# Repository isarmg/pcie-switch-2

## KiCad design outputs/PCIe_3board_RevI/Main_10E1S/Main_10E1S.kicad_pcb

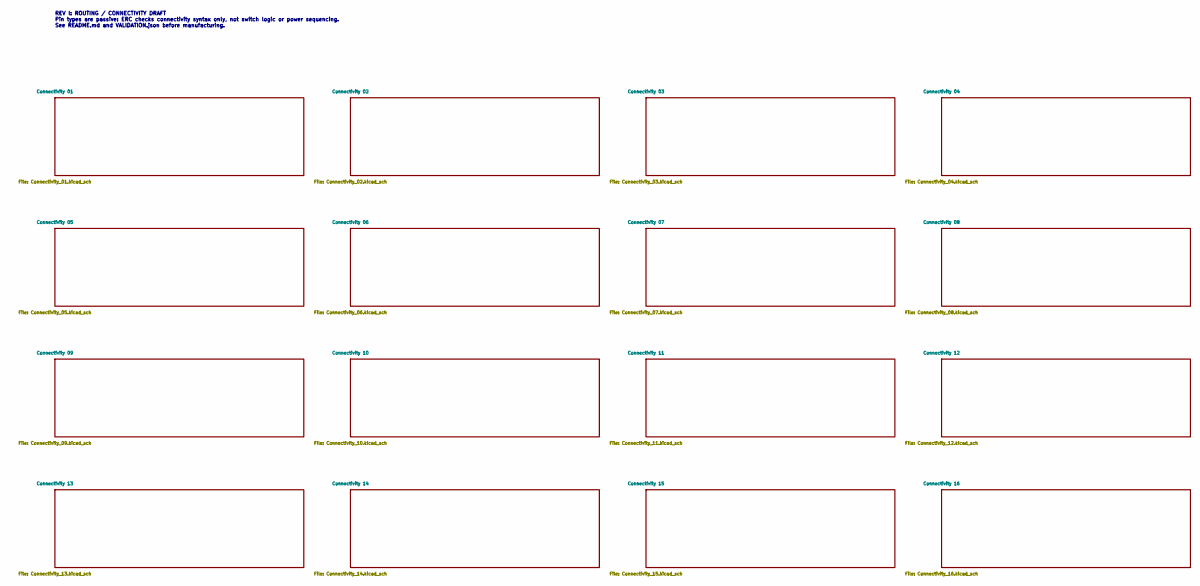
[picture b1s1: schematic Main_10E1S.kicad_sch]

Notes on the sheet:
REV I: ROUTING / CONNECTIVITY DRAFT Pin types are passive: ERC checks connectivity syntax only, not switch logic or power sequencing. See README.md and VALIDATION.json before manufacturing.

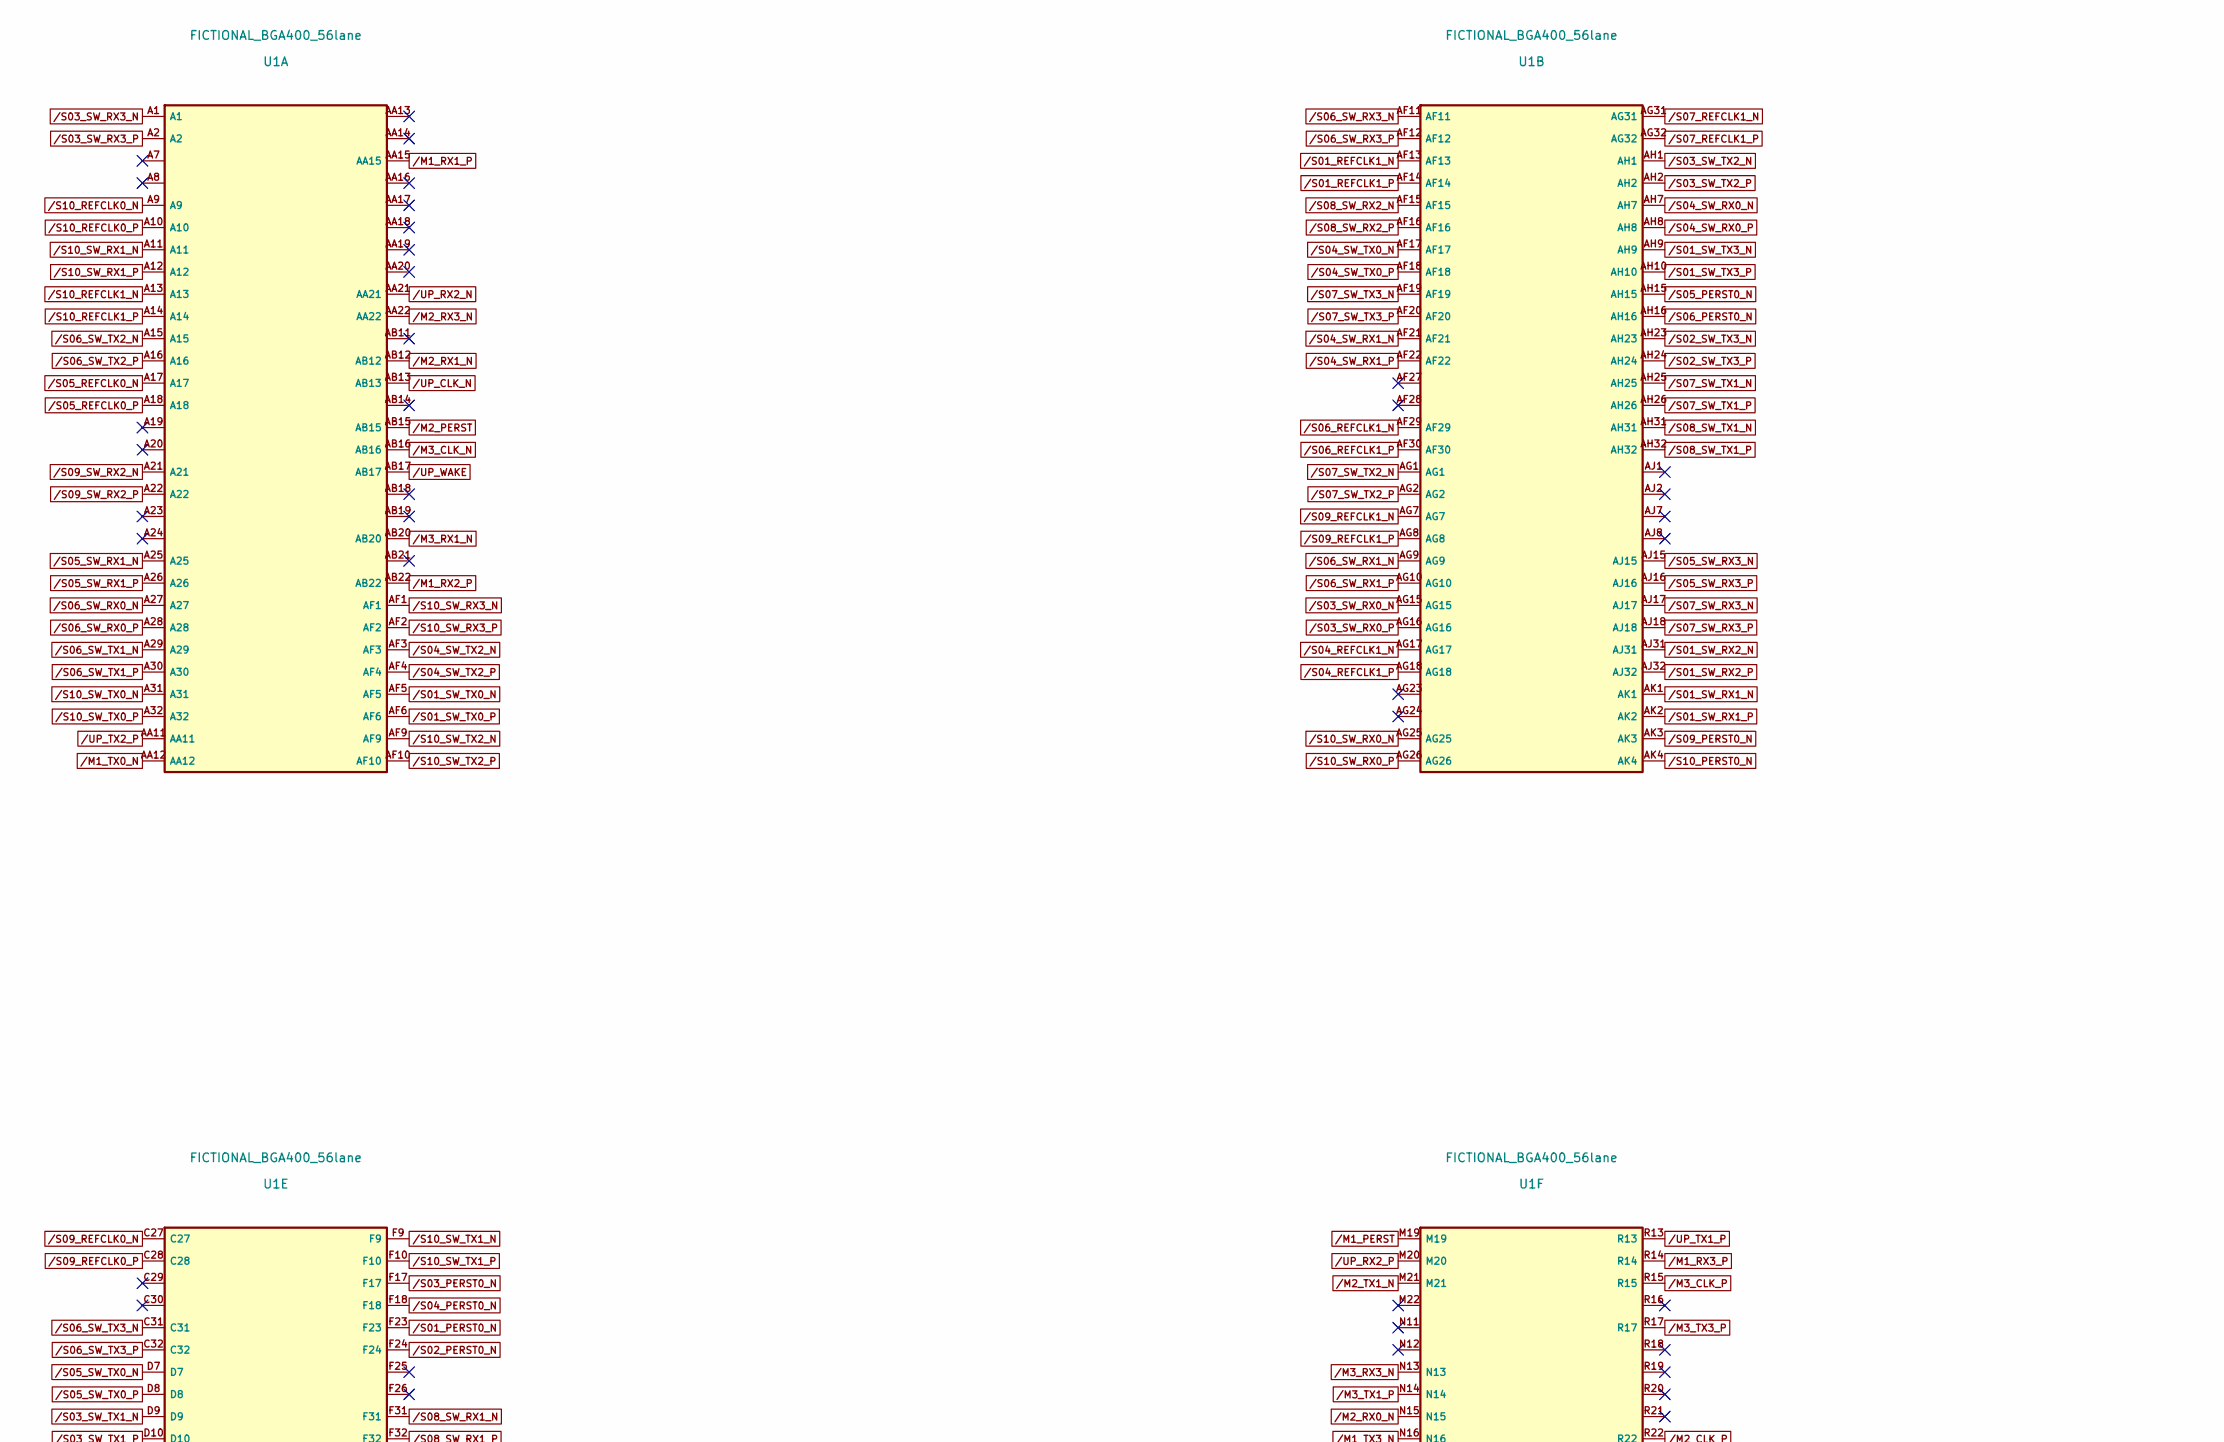
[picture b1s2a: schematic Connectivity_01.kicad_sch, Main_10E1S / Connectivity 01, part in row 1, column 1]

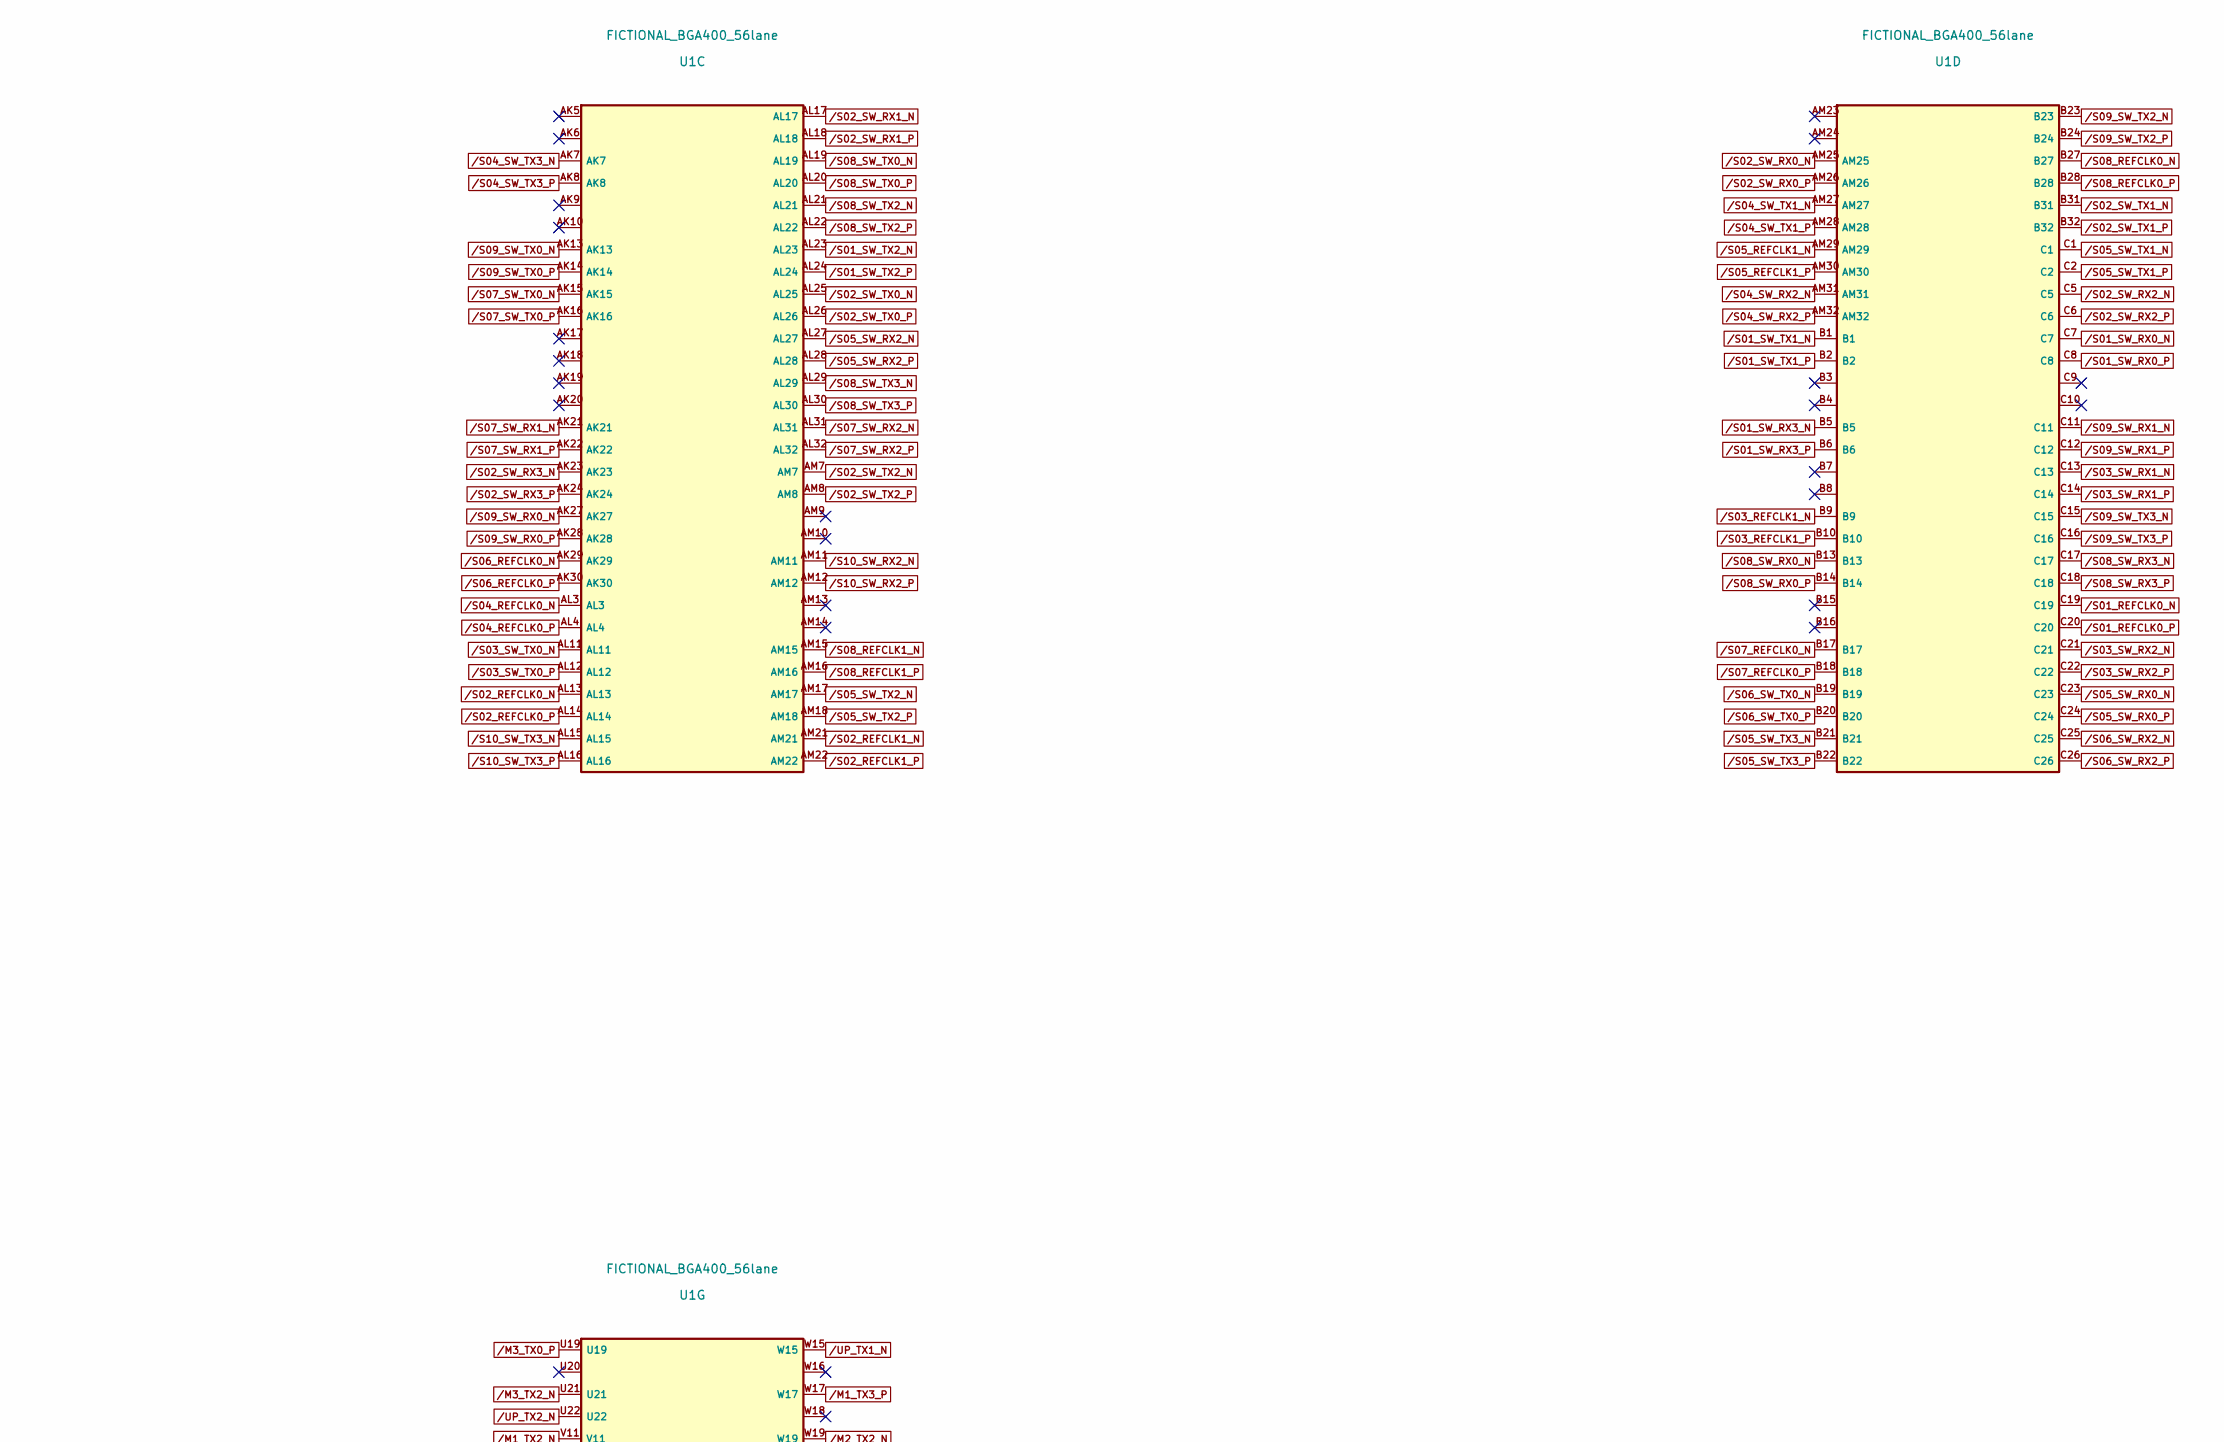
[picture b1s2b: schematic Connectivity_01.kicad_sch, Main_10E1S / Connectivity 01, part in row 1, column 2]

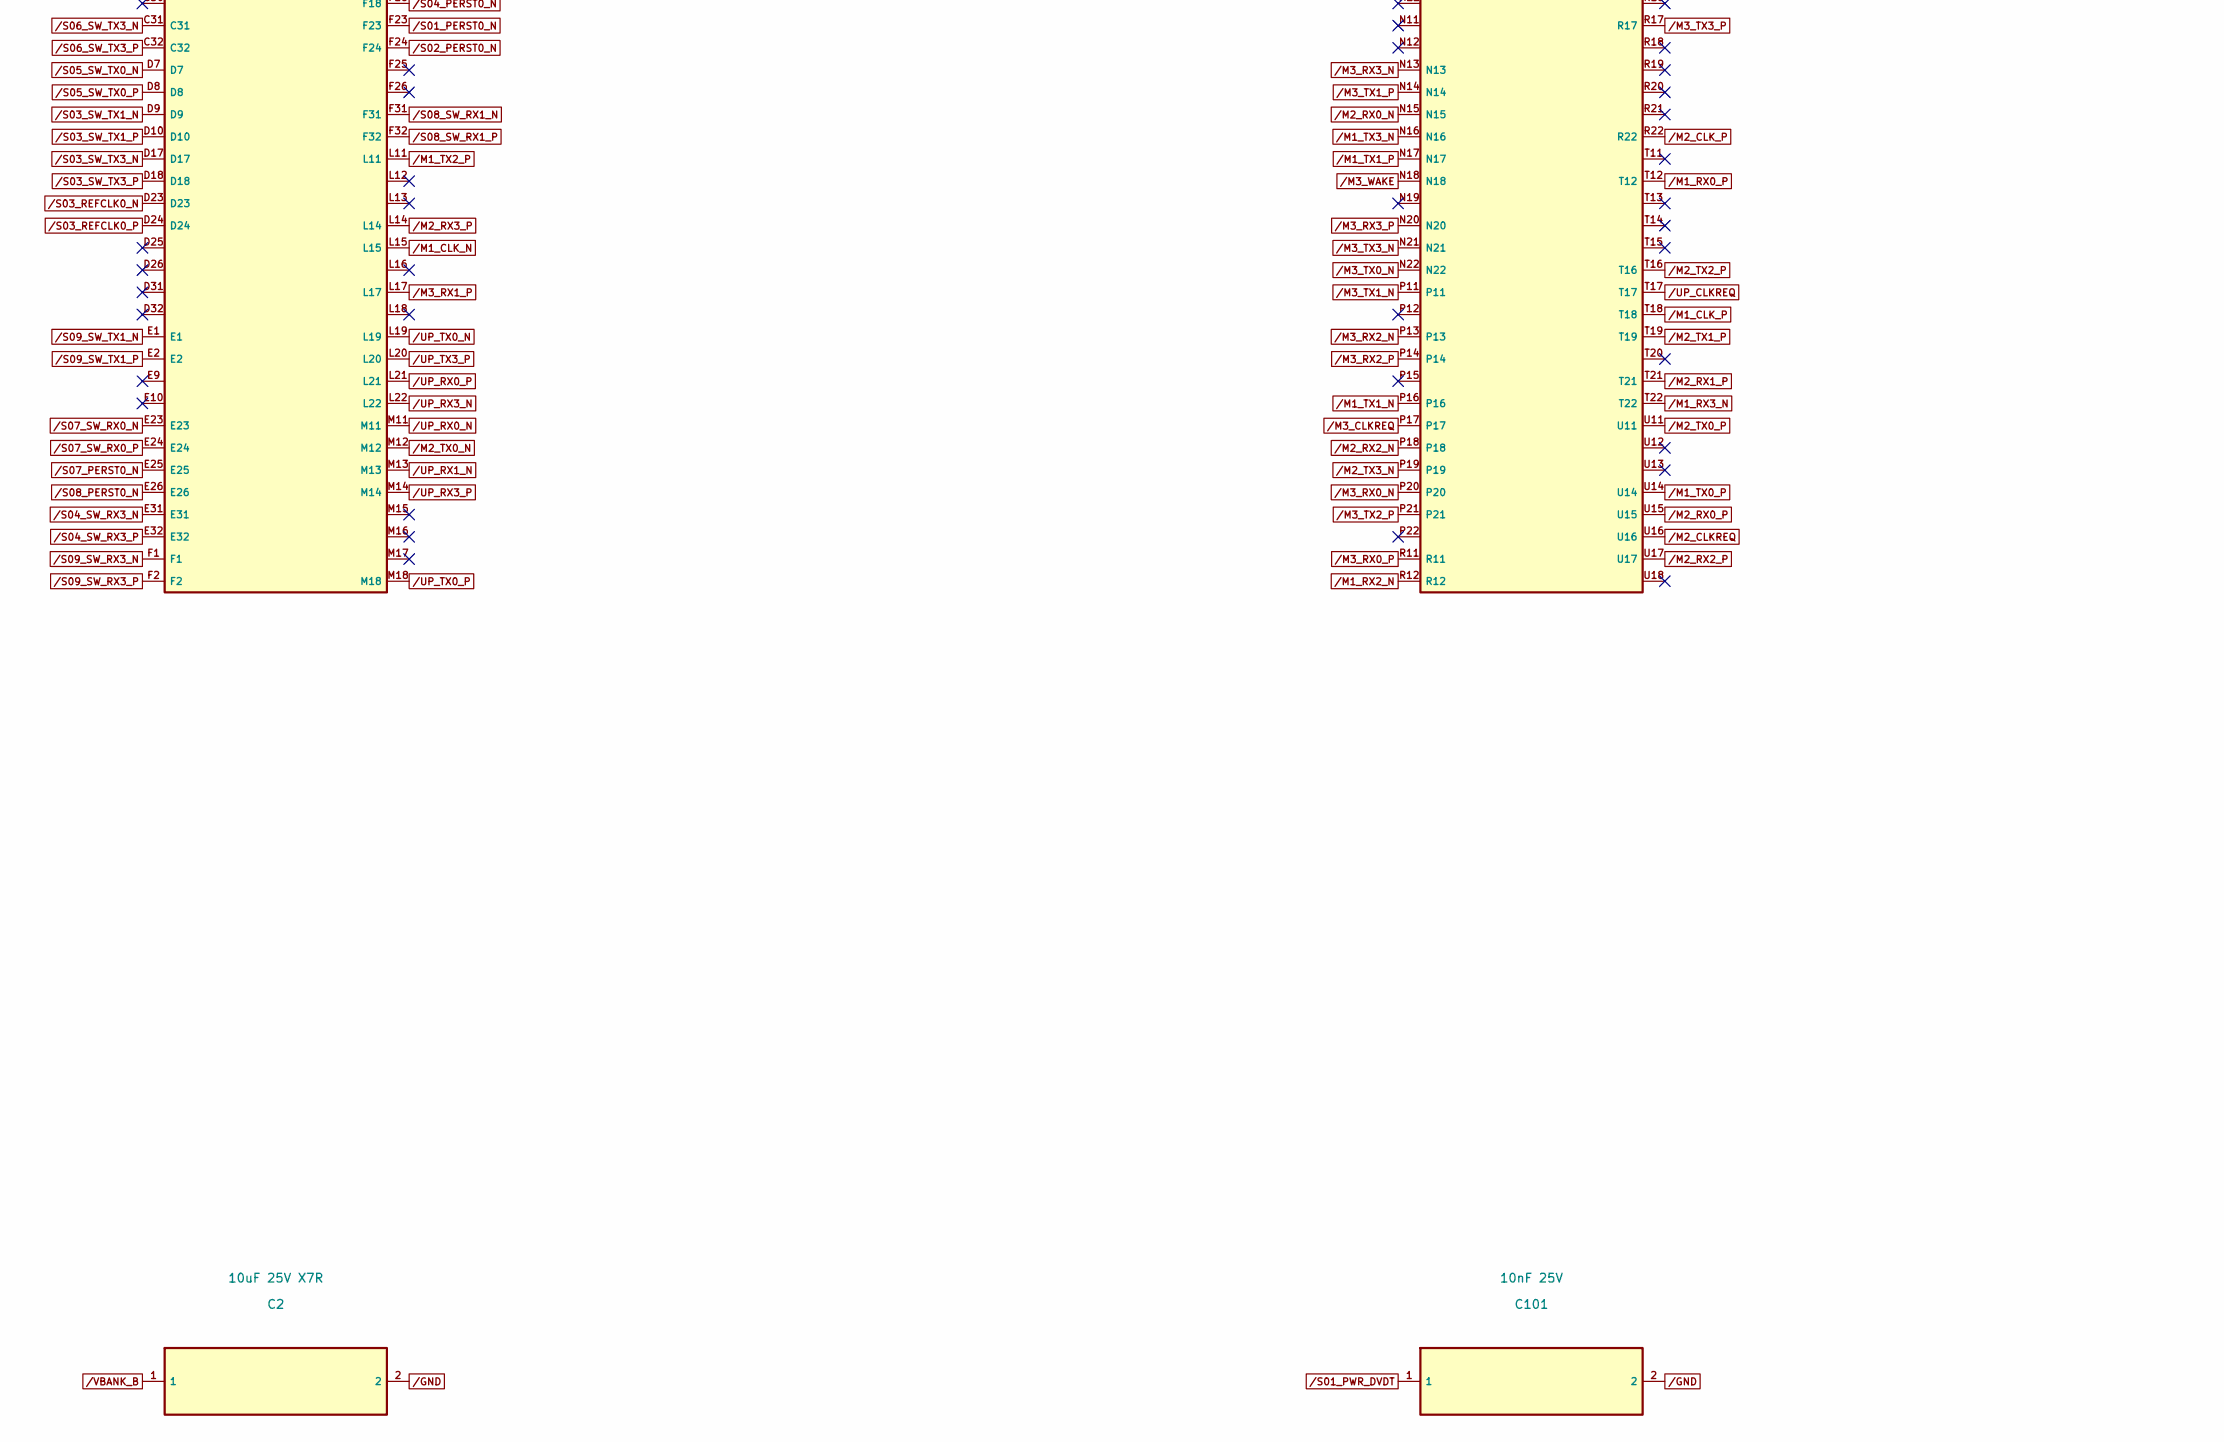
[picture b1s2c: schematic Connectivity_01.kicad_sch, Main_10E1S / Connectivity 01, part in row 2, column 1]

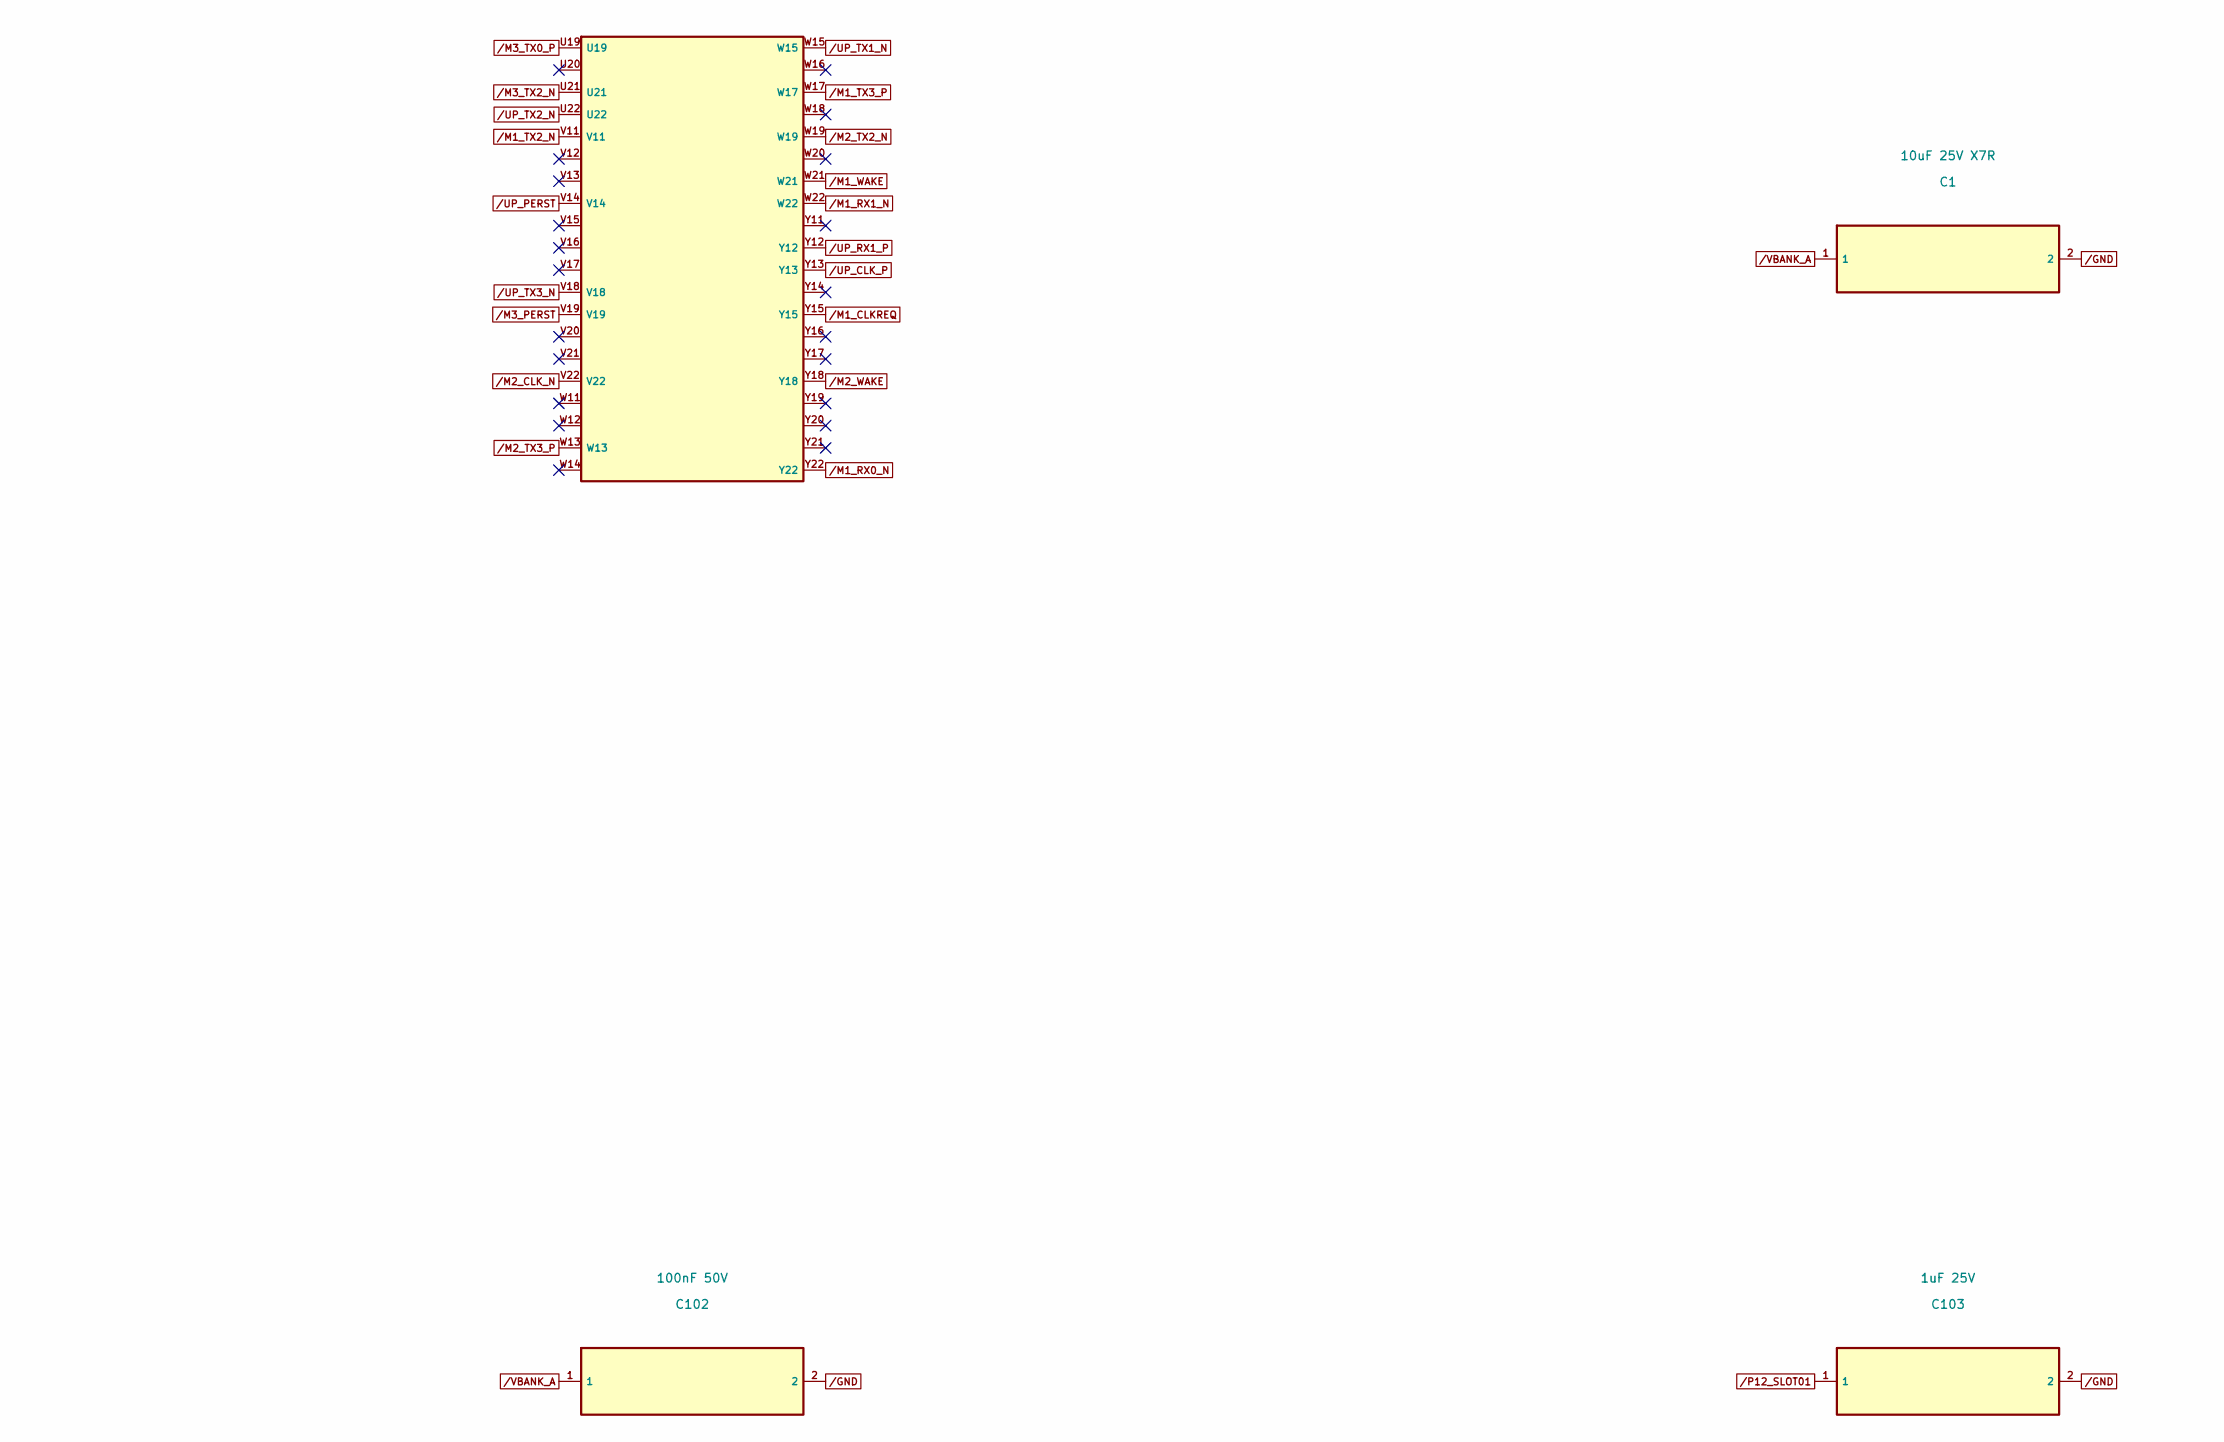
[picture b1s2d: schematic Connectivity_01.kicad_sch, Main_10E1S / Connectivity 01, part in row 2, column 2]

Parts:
C1, C2: 10uF 25V X7R; C_1210_3225Metric
C101: 10nF 25V; C_0402_1005Metric
C102: 100nF 50V; C_0603_1608Metric
C103: 1uF 25V; C_0603_1608Metric
U1: FICTIONAL_BGA400_56lane

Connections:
/GND: C1.2, C2.2, C101.2, C102.2, C103.2; also elsewhere on the board
/M1_CLKREQ: U1.Y15; also elsewhere on the board
/M1_CLK_N: U1.L15; also elsewhere on the board
/M1_CLK_P: U1.T18; also elsewhere on the board
/M1_PERST: U1.M19; also elsewhere on the board
/M1_RX0_N: U1.Y22; also elsewhere on the board
/M1_RX0_P: U1.T12; also elsewhere on the board
/M1_RX1_N: U1.W22; also elsewhere on the board
/M1_RX1_P: U1.AA15; also elsewhere on the board
/M1_RX2_N: U1.R12; also elsewhere on the board
/M1_RX2_P: U1.AB22; also elsewhere on the board
/M1_RX3_N: U1.T22; also elsewhere on the board
/M1_RX3_P: U1.R14; also elsewhere on the board
/M1_TX0_N: U1.AA12; also elsewhere on the board
/M1_TX0_P: U1.U14; also elsewhere on the board
/M1_TX1_N: U1.P16; also elsewhere on the board
/M1_TX1_P: U1.N17; also elsewhere on the board
/M1_TX2_N: U1.V11; also elsewhere on the board
/M1_TX2_P: U1.L11; also elsewhere on the board
/M1_TX3_N: U1.N16; also elsewhere on the board
/M1_TX3_P: U1.W17; also elsewhere on the board
/M1_WAKE: U1.W21; also elsewhere on the board
/M2_CLKREQ: U1.U16; also elsewhere on the board
/M2_CLK_N: U1.V22; also elsewhere on the board
/M2_CLK_P: U1.R22; also elsewhere on the board
/M2_PERST: U1.AB15; also elsewhere on the board
/M2_RX0_N: U1.N15; also elsewhere on the board
/M2_RX0_P: U1.U15; also elsewhere on the board
/M2_RX1_N: U1.AB12; also elsewhere on the board
/M2_RX1_P: U1.T21; also elsewhere on the board
/M2_RX2_N: U1.P18; also elsewhere on the board
/M2_RX2_P: U1.U17; also elsewhere on the board
/M2_RX3_N: U1.AA22; also elsewhere on the board
/M2_RX3_P: U1.L14; also elsewhere on the board
/M2_TX0_N: U1.M12; also elsewhere on the board
/M2_TX0_P: U1.U11; also elsewhere on the board
/M2_TX1_N: U1.M21; also elsewhere on the board
/M2_TX1_P: U1.T19; also elsewhere on the board
/M2_TX2_N: U1.W19; also elsewhere on the board
/M2_TX2_P: U1.T16; also elsewhere on the board
/M2_TX3_N: U1.P19; also elsewhere on the board
/M2_TX3_P: U1.W13; also elsewhere on the board
/M2_WAKE: U1.Y18; also elsewhere on the board
/M3_CLKREQ: U1.P17; also elsewhere on the board
/M3_CLK_N: U1.AB16; also elsewhere on the board
/M3_CLK_P: U1.R15; also elsewhere on the board
/M3_PERST: U1.V19; also elsewhere on the board
/M3_RX0_N: U1.P20; also elsewhere on the board
/M3_RX0_P: U1.R11; also elsewhere on the board
/M3_RX1_N: U1.AB20; also elsewhere on the board
/M3_RX1_P: U1.L17; also elsewhere on the board
/M3_RX2_N: U1.P13; also elsewhere on the board
/M3_RX2_P: U1.P14; also elsewhere on the board
/M3_RX3_N: U1.N13; also elsewhere on the board
/M3_RX3_P: U1.N20; also elsewhere on the board
/M3_TX0_N: U1.N22; also elsewhere on the board
/M3_TX0_P: U1.U19; also elsewhere on the board
/M3_TX1_N: U1.P11; also elsewhere on the board
/M3_TX1_P: U1.N14; also elsewhere on the board
/M3_TX2_N: U1.U21; also elsewhere on the board
/M3_TX2_P: U1.P21; also elsewhere on the board
/M3_TX3_N: U1.N21; also elsewhere on the board
/M3_TX3_P: U1.R17; also elsewhere on the board
/M3_WAKE: U1.N18; also elsewhere on the board
/P12_SLOT01: C103.1; also elsewhere on the board
/S01_PERST0_N: U1.F23; also elsewhere on the board
/S01_PWR_DVDT: C101.1; also elsewhere on the board
/S01_REFCLK0_N: U1.C19; also elsewhere on the board
/S01_REFCLK0_P: U1.C20; also elsewhere on the board
/S01_REFCLK1_N: U1.AF13; also elsewhere on the board
/S01_REFCLK1_P: U1.AF14; also elsewhere on the board
/S01_SW_RX0_N: U1.C7; also elsewhere on the board
/S01_SW_RX0_P: U1.C8; also elsewhere on the board
/S01_SW_RX1_N: U1.AK1; also elsewhere on the board
/S01_SW_RX1_P: U1.AK2; also elsewhere on the board
/S01_SW_RX2_N: U1.AJ31; also elsewhere on the board
/S01_SW_RX2_P: U1.AJ32; also elsewhere on the board
/S01_SW_RX3_N: U1.B5; also elsewhere on the board
/S01_SW_RX3_P: U1.B6; also elsewhere on the board
/S01_SW_TX0_N: U1.AF5; also elsewhere on the board
/S01_SW_TX0_P: U1.AF6; also elsewhere on the board
/S01_SW_TX1_N: U1.B1; also elsewhere on the board
/S01_SW_TX1_P: U1.B2; also elsewhere on the board
/S01_SW_TX2_N: U1.AL23; also elsewhere on the board
/S01_SW_TX2_P: U1.AL24; also elsewhere on the board
/S01_SW_TX3_N: U1.AH9; also elsewhere on the board
/S01_SW_TX3_P: U1.AH10; also elsewhere on the board
/S02_PERST0_N: U1.F24; also elsewhere on the board
/S02_REFCLK0_N: U1.AL13; also elsewhere on the board
/S02_REFCLK0_P: U1.AL14; also elsewhere on the board
/S02_REFCLK1_N: U1.AM21; also elsewhere on the board
/S02_REFCLK1_P: U1.AM22; also elsewhere on the board
/S02_SW_RX0_N: U1.AM25; also elsewhere on the board
/S02_SW_RX0_P: U1.AM26; also elsewhere on the board
/S02_SW_RX1_N: U1.AL17; also elsewhere on the board
/S02_SW_RX1_P: U1.AL18; also elsewhere on the board
/S02_SW_RX2_N: U1.C5; also elsewhere on the board
/S02_SW_RX2_P: U1.C6; also elsewhere on the board
/S02_SW_RX3_N: U1.AK23; also elsewhere on the board
/S02_SW_RX3_P: U1.AK24; also elsewhere on the board
/S02_SW_TX0_N: U1.AL25; also elsewhere on the board
/S02_SW_TX0_P: U1.AL26; also elsewhere on the board
/S02_SW_TX1_N: U1.B31; also elsewhere on the board
/S02_SW_TX1_P: U1.B32; also elsewhere on the board
/S02_SW_TX2_N: U1.AM7; also elsewhere on the board
/S02_SW_TX2_P: U1.AM8; also elsewhere on the board
/S02_SW_TX3_N: U1.AH23; also elsewhere on the board
/S02_SW_TX3_P: U1.AH24; also elsewhere on the board
/S03_PERST0_N: U1.F17; also elsewhere on the board
/S03_REFCLK0_N: U1.D23; also elsewhere on the board
/S03_REFCLK0_P: U1.D24; also elsewhere on the board
/S03_REFCLK1_N: U1.B9; also elsewhere on the board
/S03_REFCLK1_P: U1.B10; also elsewhere on the board
/S03_SW_RX0_N: U1.AG15; also elsewhere on the board
/S03_SW_RX0_P: U1.AG16; also elsewhere on the board
/S03_SW_RX1_N: U1.C13; also elsewhere on the board
/S03_SW_RX1_P: U1.C14; also elsewhere on the board
/S03_SW_RX2_N: U1.C21; also elsewhere on the board
/S03_SW_RX2_P: U1.C22; also elsewhere on the board
/S03_SW_RX3_N: U1.A1; also elsewhere on the board
/S03_SW_RX3_P: U1.A2; also elsewhere on the board
/S03_SW_TX0_N: U1.AL11; also elsewhere on the board
/S03_SW_TX0_P: U1.AL12; also elsewhere on the board
/S03_SW_TX1_N: U1.D9; also elsewhere on the board
/S03_SW_TX1_P: U1.D10; also elsewhere on the board
/S03_SW_TX2_N: U1.AH1; also elsewhere on the board
/S03_SW_TX2_P: U1.AH2; also elsewhere on the board
/S03_SW_TX3_N: U1.D17; also elsewhere on the board
/S03_SW_TX3_P: U1.D18; also elsewhere on the board
/S04_PERST0_N: U1.F18; also elsewhere on the board
/S04_REFCLK0_N: U1.AL3; also elsewhere on the board
/S04_REFCLK0_P: U1.AL4; also elsewhere on the board
/S04_REFCLK1_N: U1.AG17; also elsewhere on the board
/S04_REFCLK1_P: U1.AG18; also elsewhere on the board
/S04_SW_RX0_N: U1.AH7; also elsewhere on the board
/S04_SW_RX0_P: U1.AH8; also elsewhere on the board
/S04_SW_RX1_N: U1.AF21; also elsewhere on the board
/S04_SW_RX1_P: U1.AF22; also elsewhere on the board
/S04_SW_RX2_N: U1.AM31; also elsewhere on the board
/S04_SW_RX2_P: U1.AM32; also elsewhere on the board
/S04_SW_RX3_N: U1.E31; also elsewhere on the board
/S04_SW_RX3_P: U1.E32; also elsewhere on the board
/S04_SW_TX0_N: U1.AF17; also elsewhere on the board
/S04_SW_TX0_P: U1.AF18; also elsewhere on the board
/S04_SW_TX1_N: U1.AM27; also elsewhere on the board
/S04_SW_TX1_P: U1.AM28; also elsewhere on the board
/S04_SW_TX2_N: U1.AF3; also elsewhere on the board
/S04_SW_TX2_P: U1.AF4; also elsewhere on the board
/S04_SW_TX3_N: U1.AK7; also elsewhere on the board
/S04_SW_TX3_P: U1.AK8; also elsewhere on the board
/S05_PERST0_N: U1.AH15; also elsewhere on the board
/S05_REFCLK0_N: U1.A17; also elsewhere on the board
/S05_REFCLK0_P: U1.A18; also elsewhere on the board
/S05_REFCLK1_N: U1.AM29; also elsewhere on the board
/S05_REFCLK1_P: U1.AM30; also elsewhere on the board
/S05_SW_RX0_N: U1.C23; also elsewhere on the board
/S05_SW_RX0_P: U1.C24; also elsewhere on the board
/S05_SW_RX1_N: U1.A25; also elsewhere on the board
/S05_SW_RX1_P: U1.A26; also elsewhere on the board
/S05_SW_RX2_N: U1.AL27; also elsewhere on the board
/S05_SW_RX2_P: U1.AL28; also elsewhere on the board
/S05_SW_RX3_N: U1.AJ15; also elsewhere on the board
/S05_SW_RX3_P: U1.AJ16; also elsewhere on the board
/S05_SW_TX0_N: U1.D7; also elsewhere on the board
/S05_SW_TX0_P: U1.D8; also elsewhere on the board
/S05_SW_TX1_N: U1.C1; also elsewhere on the board
/S05_SW_TX1_P: U1.C2; also elsewhere on the board
/S05_SW_TX2_N: U1.AM17; also elsewhere on the board
/S05_SW_TX2_P: U1.AM18; also elsewhere on the board
/S05_SW_TX3_N: U1.B21; also elsewhere on the board
/S05_SW_TX3_P: U1.B22; also elsewhere on the board
/S06_PERST0_N: U1.AH16; also elsewhere on the board
/S06_REFCLK0_N: U1.AK29; also elsewhere on the board
/S06_REFCLK0_P: U1.AK30; also elsewhere on the board
/S06_REFCLK1_N: U1.AF29; also elsewhere on the board
/S06_REFCLK1_P: U1.AF30; also elsewhere on the board
/S06_SW_RX0_N: U1.A27; also elsewhere on the board
/S06_SW_RX0_P: U1.A28; also elsewhere on the board
/S06_SW_RX1_N: U1.AG9; also elsewhere on the board
/S06_SW_RX1_P: U1.AG10; also elsewhere on the board
/S06_SW_RX2_N: U1.C25; also elsewhere on the board
/S06_SW_RX2_P: U1.C26; also elsewhere on the board
/S06_SW_RX3_N: U1.AF11; also elsewhere on the board
/S06_SW_RX3_P: U1.AF12; also elsewhere on the board
/S06_SW_TX0_N: U1.B19; also elsewhere on the board
/S06_SW_TX0_P: U1.B20; also elsewhere on the board
/S06_SW_TX1_N: U1.A29; also elsewhere on the board
/S06_SW_TX1_P: U1.A30; also elsewhere on the board
/S06_SW_TX2_N: U1.A15; also elsewhere on the board
/S06_SW_TX2_P: U1.A16; also elsewhere on the board
/S06_SW_TX3_N: U1.C31; also elsewhere on the board
/S06_SW_TX3_P: U1.C32; also elsewhere on the board
/S07_PERST0_N: U1.E25; also elsewhere on the board
/S07_REFCLK0_N: U1.B17; also elsewhere on the board
/S07_REFCLK0_P: U1.B18; also elsewhere on the board
/S07_REFCLK1_N: U1.AG31; also elsewhere on the board
/S07_REFCLK1_P: U1.AG32; also elsewhere on the board
/S07_SW_RX0_N: U1.E23; also elsewhere on the board
/S07_SW_RX0_P: U1.E24; also elsewhere on the board
/S07_SW_RX1_N: U1.AK21; also elsewhere on the board
/S07_SW_RX1_P: U1.AK22; also elsewhere on the board
/S07_SW_RX2_N: U1.AL31; also elsewhere on the board
/S07_SW_RX2_P: U1.AL32; also elsewhere on the board
/S07_SW_RX3_N: U1.AJ17; also elsewhere on the board
/S07_SW_RX3_P: U1.AJ18; also elsewhere on the board
/S07_SW_TX0_N: U1.AK15; also elsewhere on the board
/S07_SW_TX0_P: U1.AK16; also elsewhere on the board
/S07_SW_TX1_N: U1.AH25; also elsewhere on the board
/S07_SW_TX1_P: U1.AH26; also elsewhere on the board
/S07_SW_TX2_N: U1.AG1; also elsewhere on the board
/S07_SW_TX2_P: U1.AG2; also elsewhere on the board
/S07_SW_TX3_N: U1.AF19; also elsewhere on the board
/S07_SW_TX3_P: U1.AF20; also elsewhere on the board
/S08_PERST0_N: U1.E26; also elsewhere on the board
/S08_REFCLK0_N: U1.B27; also elsewhere on the board
/S08_REFCLK0_P: U1.B28; also elsewhere on the board
/S08_REFCLK1_N: U1.AM15; also elsewhere on the board
/S08_REFCLK1_P: U1.AM16; also elsewhere on the board
/S08_SW_RX0_N: U1.B13; also elsewhere on the board
/S08_SW_RX0_P: U1.B14; also elsewhere on the board
/S08_SW_RX1_N: U1.F31; also elsewhere on the board
/S08_SW_RX1_P: U1.F32; also elsewhere on the board
/S08_SW_RX2_N: U1.AF15; also elsewhere on the board
/S08_SW_RX2_P: U1.AF16; also elsewhere on the board
/S08_SW_RX3_N: U1.C17; also elsewhere on the board
/S08_SW_RX3_P: U1.C18; also elsewhere on the board
/S08_SW_TX0_N: U1.AL19; also elsewhere on the board
/S08_SW_TX0_P: U1.AL20; also elsewhere on the board
/S08_SW_TX1_N: U1.AH31; also elsewhere on the board
/S08_SW_TX1_P: U1.AH32; also elsewhere on the board
/S08_SW_TX2_N: U1.AL21; also elsewhere on the board
/S08_SW_TX2_P: U1.AL22; also elsewhere on the board
/S08_SW_TX3_N: U1.AL29; also elsewhere on the board
/S08_SW_TX3_P: U1.AL30; also elsewhere on the board
/S09_PERST0_N: U1.AK3; also elsewhere on the board
/S09_REFCLK0_N: U1.C27; also elsewhere on the board
/S09_REFCLK0_P: U1.C28; also elsewhere on the board
/S09_REFCLK1_N: U1.AG7; also elsewhere on the board
/S09_REFCLK1_P: U1.AG8; also elsewhere on the board
/S09_SW_RX0_N: U1.AK27; also elsewhere on the board
/S09_SW_RX0_P: U1.AK28; also elsewhere on the board
/S09_SW_RX1_N: U1.C11; also elsewhere on the board
/S09_SW_RX1_P: U1.C12; also elsewhere on the board
/S09_SW_RX2_N: U1.A21; also elsewhere on the board
/S09_SW_RX2_P: U1.A22; also elsewhere on the board
/S09_SW_RX3_N: U1.F1; also elsewhere on the board
/S09_SW_RX3_P: U1.F2; also elsewhere on the board
/S09_SW_TX0_N: U1.AK13; also elsewhere on the board
/S09_SW_TX0_P: U1.AK14; also elsewhere on the board
/S09_SW_TX1_N: U1.E1; also elsewhere on the board
/S09_SW_TX1_P: U1.E2; also elsewhere on the board
/S09_SW_TX2_N: U1.B23; also elsewhere on the board
/S09_SW_TX2_P: U1.B24; also elsewhere on the board
/S09_SW_TX3_N: U1.C15; also elsewhere on the board
/S09_SW_TX3_P: U1.C16; also elsewhere on the board
/S10_PERST0_N: U1.AK4; also elsewhere on the board
/S10_REFCLK0_N: U1.A9; also elsewhere on the board
/S10_REFCLK0_P: U1.A10; also elsewhere on the board
/S10_REFCLK1_N: U1.A13; also elsewhere on the board
/S10_REFCLK1_P: U1.A14; also elsewhere on the board
/S10_SW_RX0_N: U1.AG25; also elsewhere on the board
/S10_SW_RX0_P: U1.AG26; also elsewhere on the board
/S10_SW_RX1_N: U1.A11; also elsewhere on the board
/S10_SW_RX1_P: U1.A12; also elsewhere on the board
/S10_SW_RX2_N: U1.AM11; also elsewhere on the board
/S10_SW_RX2_P: U1.AM12; also elsewhere on the board
/S10_SW_RX3_N: U1.AF1; also elsewhere on the board
/S10_SW_RX3_P: U1.AF2; also elsewhere on the board
/S10_SW_TX0_N: U1.A31; also elsewhere on the board
/S10_SW_TX0_P: U1.A32; also elsewhere on the board
/S10_SW_TX1_N: U1.F9; also elsewhere on the board
/S10_SW_TX1_P: U1.F10; also elsewhere on the board
/S10_SW_TX2_N: U1.AF9; also elsewhere on the board
/S10_SW_TX2_P: U1.AF10; also elsewhere on the board
/S10_SW_TX3_N: U1.AL15; also elsewhere on the board
/S10_SW_TX3_P: U1.AL16; also elsewhere on the board
/UP_CLKREQ: U1.T17; also elsewhere on the board
/UP_CLK_N: U1.AB13; also elsewhere on the board
/UP_CLK_P: U1.Y13; also elsewhere on the board
/UP_PERST: U1.V14; also elsewhere on the board
/UP_RX0_N: U1.M11; also elsewhere on the board
/UP_RX0_P: U1.L21; also elsewhere on the board
/UP_RX1_N: U1.M13; also elsewhere on the board
/UP_RX1_P: U1.Y12; also elsewhere on the board
/UP_RX2_N: U1.AA21; also elsewhere on the board
/UP_RX2_P: U1.M20; also elsewhere on the board
/UP_RX3_N: U1.L22; also elsewhere on the board
/UP_RX3_P: U1.M14; also elsewhere on the board
/UP_TX0_N: U1.L19; also elsewhere on the board
/UP_TX0_P: U1.M18; also elsewhere on the board
/UP_TX1_N: U1.W15; also elsewhere on the board
/UP_TX1_P: U1.R13; also elsewhere on the board
/UP_TX2_N: U1.U22; also elsewhere on the board
/UP_TX2_P: U1.AA11; also elsewhere on the board
/UP_TX3_N: U1.V18; also elsewhere on the board
/UP_TX3_P: U1.L20; also elsewhere on the board
/UP_WAKE: U1.AB17; also elsewhere on the board
/VBANK_A: C1.1, C102.1; also elsewhere on the board
/VBANK_B: C2.1; also elsewhere on the board
